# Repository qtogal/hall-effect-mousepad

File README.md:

Readme for the halleffectmousepad project.

This project aims to create a mousepad that includes a grid of hall effect sensors to detect magnets. The values of each will be interpreted by a program to calculate the position of the magnet even if it is not on the exact position of a sensor. 

# BOM
 |Part|QTY|
 |---|---|
 |SS49E Hall Effect Sensor|24|
 |CD74HC4067SE analog mux|3|
 |AMS1117-3.3 regulator|1|
 |Neodyum magnets 12mm diameter*2mm|1|
 |0.1 uF capacitor|3|
 |10uF capacitor|2|
 |3D printed case|1|
 |3D printed magnet casing|1|
 |usb cable|1|

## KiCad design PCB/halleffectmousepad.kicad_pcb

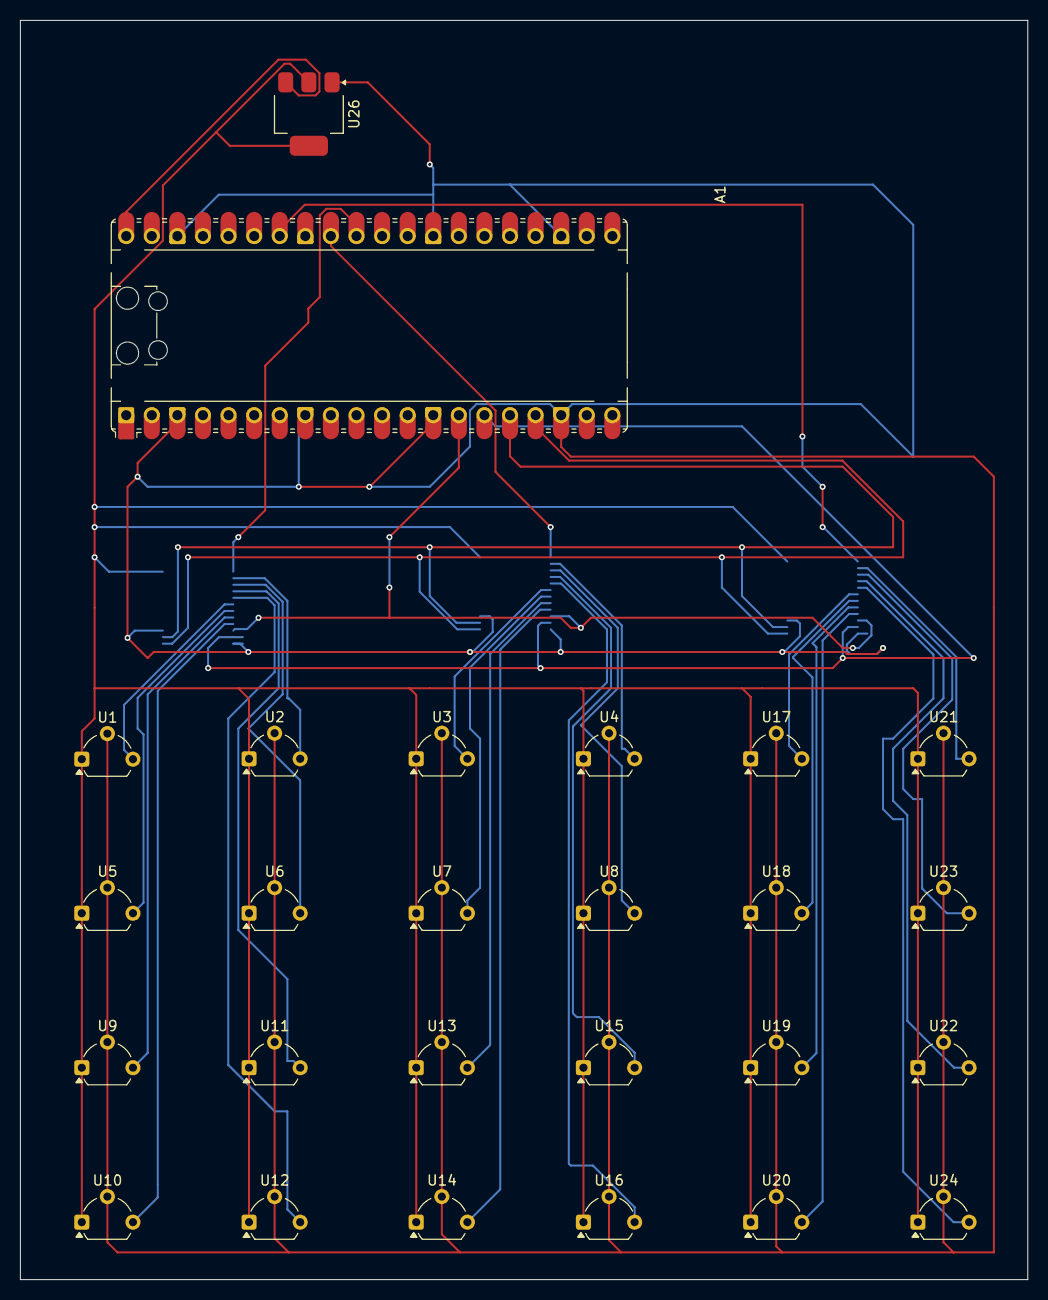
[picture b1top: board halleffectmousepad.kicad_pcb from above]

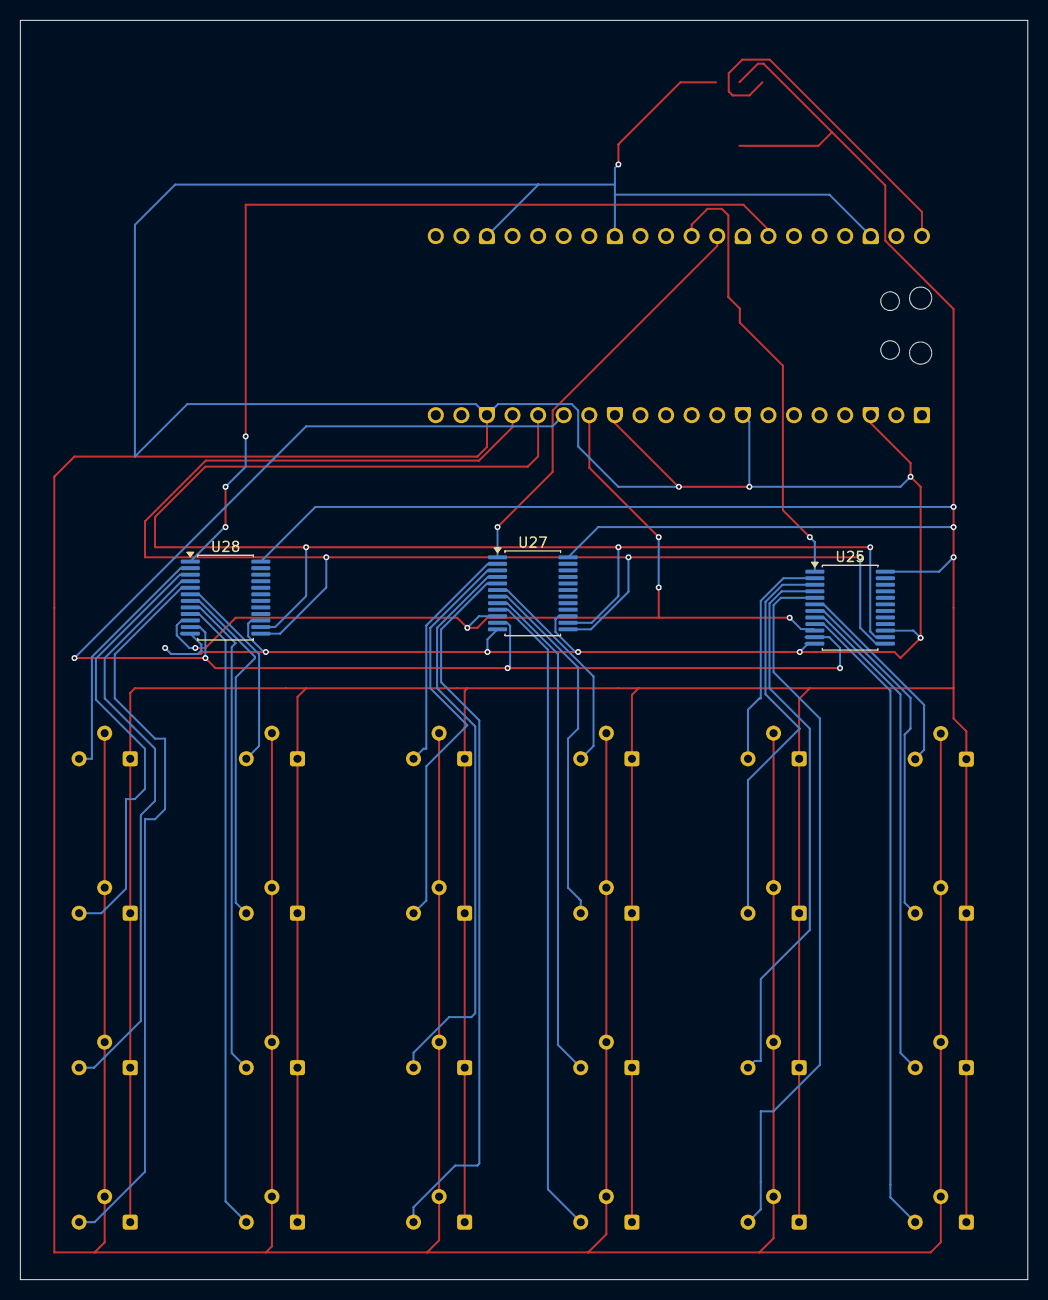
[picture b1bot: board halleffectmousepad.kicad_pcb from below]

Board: 2 copper layers, 100.0 x 125.0 mm, 29 parts (3 on the bottom side), 34 nets.

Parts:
A1: RaspberryPi_Pico; RaspberryPi_Pico_Common_Unspecified
U1, U2, U3, U4, U5, U6, U7, U8, U9, U10, U11, U12, U13, U14, U15, U16, U17, U18, U19, U20, U21, U22, U23, U24: TO-92L_Wide
U25, U27, U28: CD74HC4067SM; SSOP-24_5.3x8.2mm_P0.65mm
U26: AMS1117-3.3; SOT-223-3_TabPin2

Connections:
/GND: A1.3 (GND), A1.8 (GND), A1.13 (GND), A1.18 (GND), A1.23 (GND), A1.28 (GND), A1.38 (GND), U1.2 (GND), U2.2 (GND), U3.2 (GND), U4.2 (GND), U5.2 (GND), U6.2 (GND), U7.2 (GND), U8.2 (GND), U9.2 (GND), U10.2 (GND), U11.2 (GND), U12.2 (GND), U13.2 (GND), U14.2 (GND), U15.2 (GND), U16.2 (GND), U17.2 (GND), U18.2 (GND), U19.2 (GND), U20.2 (GND), U21.2 (GND), U22.2 (GND), U23.2 (GND), U24.2 (GND), U25.12 (GND), U25.15 (~E), U26.1 (GND), U27.12 (GND), U27.15 (~E), U28.12 (GND), U28.15 (~E)
/S0: A1.14 (GPIO10), U25.10 (S0), U27.10 (S0), U28.10 (S0)
/S1: A1.15 (GPIO11), U25.11 (S1), U27.11 (S1), U28.11 (S1)
/S2: A1.16 (GPIO12), U25.14 (S2), U27.14 (S2), U28.14 (S2)
/S3: A1.17 (GPIO13), U25.13 (S3), U27.13 (S3), U28.13 (S3)
/VCC: U1.1 (VCC), U2.1 (VCC), U3.1 (VCC), U4.1 (VCC), U5.1 (VCC), U6.1 (VCC), U7.1 (VCC), U8.1 (VCC), U9.1 (VCC), U10.1 (VCC), U11.1 (VCC), U12.1 (VCC), U13.1 (VCC), U14.1 (VCC), U15.1 (VCC), U16.1 (VCC), U17.1 (VCC), U18.1 (VCC), U19.1 (VCC), U20.1 (VCC), U21.1 (VCC), U22.1 (VCC), U23.1 (VCC), U24.1 (VCC), U25.24 (VCC), U26.2 (VO), U27.24 (VCC), U28.24 (VCC)
unnamed: A1.31 (GPIO26_ADC0), U25.1 (COM)
unnamed: A1.32 (GPIO27_ADC1), U27.1 (COM)
unnamed: A1.34 (GPIO28_ADC2), U28.1 (COM)
unnamed: A1.40 (VBUS), U26.3 (VI)
unnamed: U1.3 (Output), U25.6 (I3)
unnamed: U2.3 (Output), U25.2 (I7)
unnamed: U10.3 (Output), U25.9 (I0)
unnamed: U11.3 (Output), U25.4 (I5)
unnamed: U12.3 (Output), U25.5 (I4)
unnamed: U13.3 (Output), U27.8 (I1)
unnamed: U14.3 (Output), U27.9 (I0)
unnamed: U15.3 (Output), U27.4 (I5)
unnamed: U16.3 (Output), U27.5 (I4)
unnamed: U17.3 (Output), U28.6 (I3)
unnamed: U18.3 (Output), U28.7 (I2)
unnamed: U19.3 (Output), U28.8 (I1)
unnamed: U20.3 (Output), U28.9 (I0)
unnamed: U21.3 (Output), U28.2 (I7)
unnamed: U22.3 (Output), U28.4 (I5)
unnamed: U23.3 (Output), U28.3 (I6)
unnamed: U24.3 (Output), U28.5 (I4)
unnamed: U9.3 (Output), U25.8 (I1)
unnamed: U5.3 (Output), U25.7 (I2)
unnamed: U6.3 (Output), U25.3 (I6)
unnamed: U7.3 (Output), U27.7 (I2)
unnamed: U3.3 (Output), U27.6 (I3)
unnamed: U8.3 (Output), U27.3 (I6)
unnamed: U4.3 (Output), U27.2 (I7)
